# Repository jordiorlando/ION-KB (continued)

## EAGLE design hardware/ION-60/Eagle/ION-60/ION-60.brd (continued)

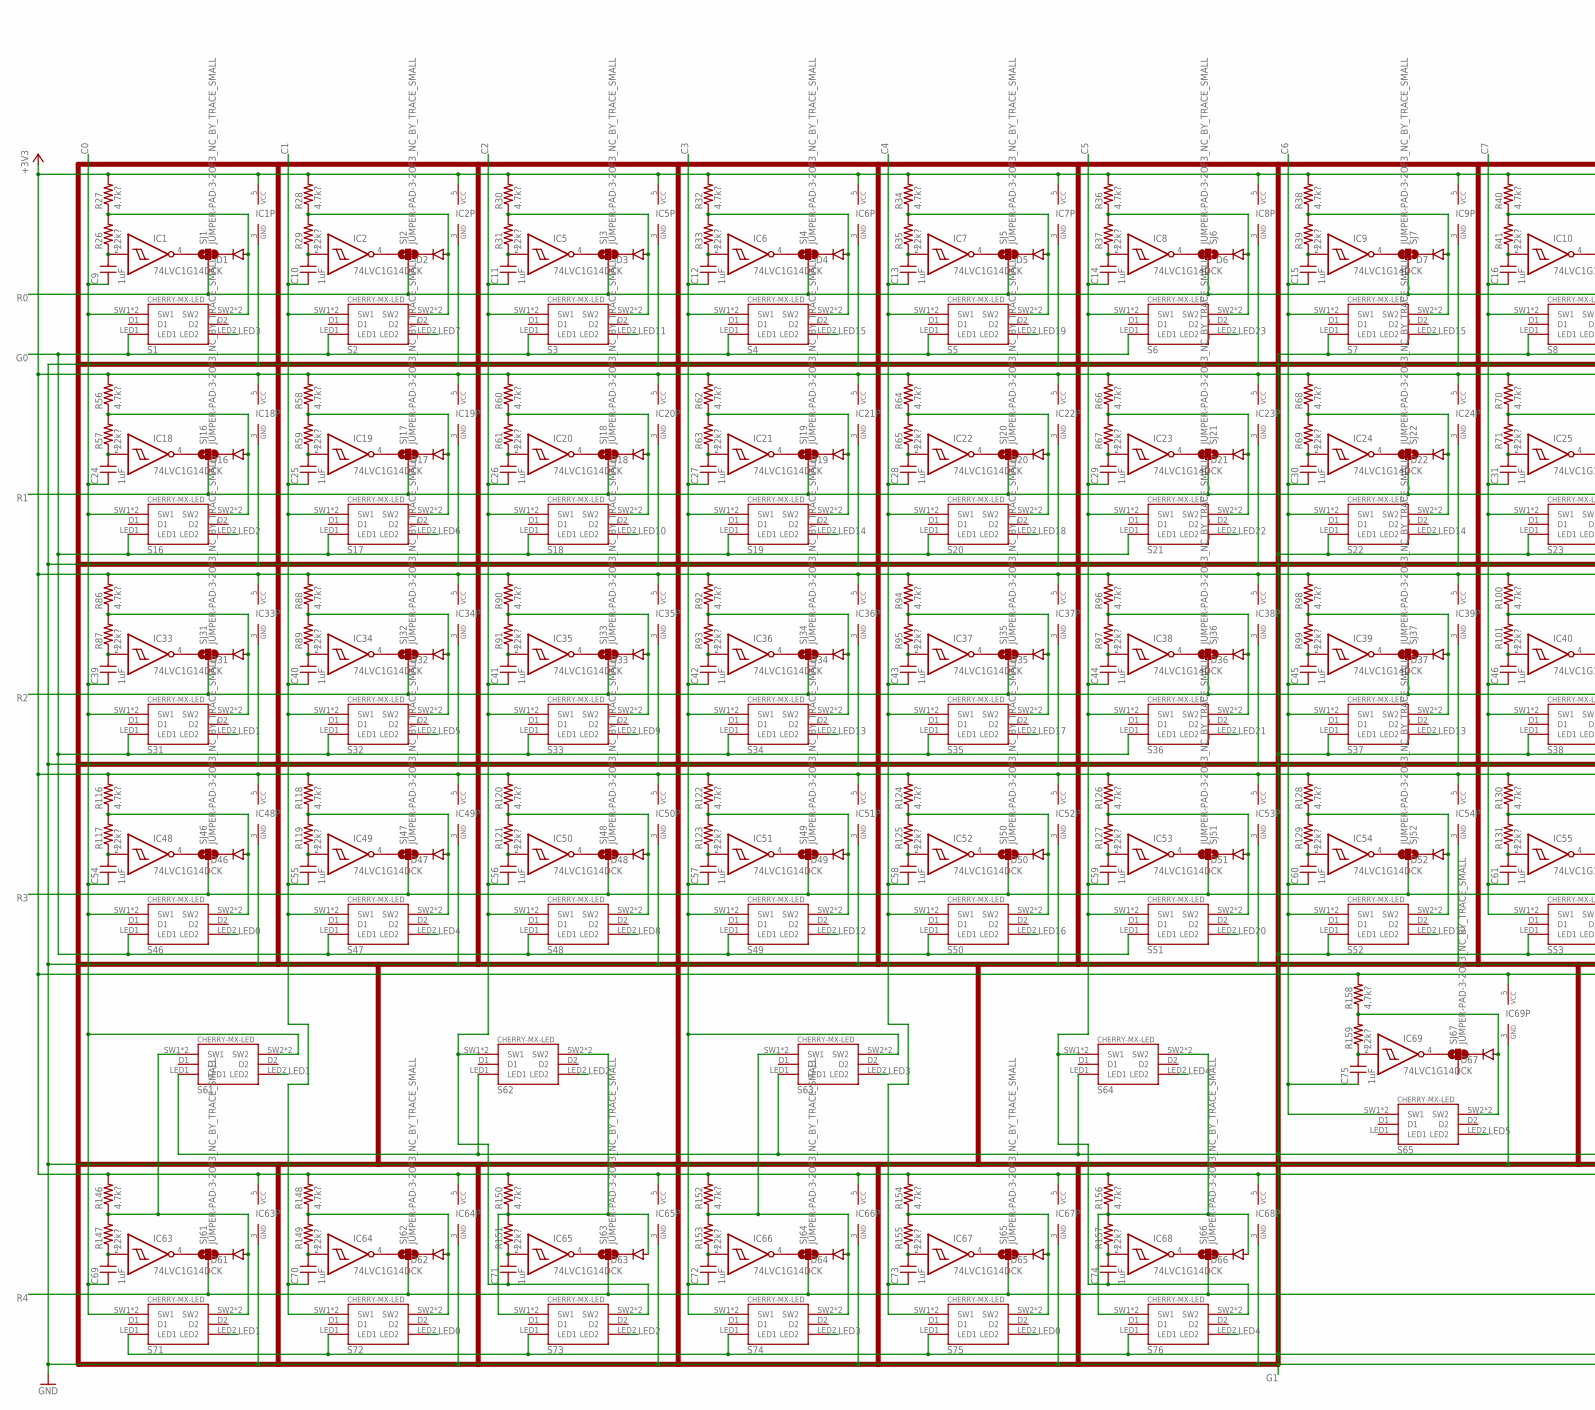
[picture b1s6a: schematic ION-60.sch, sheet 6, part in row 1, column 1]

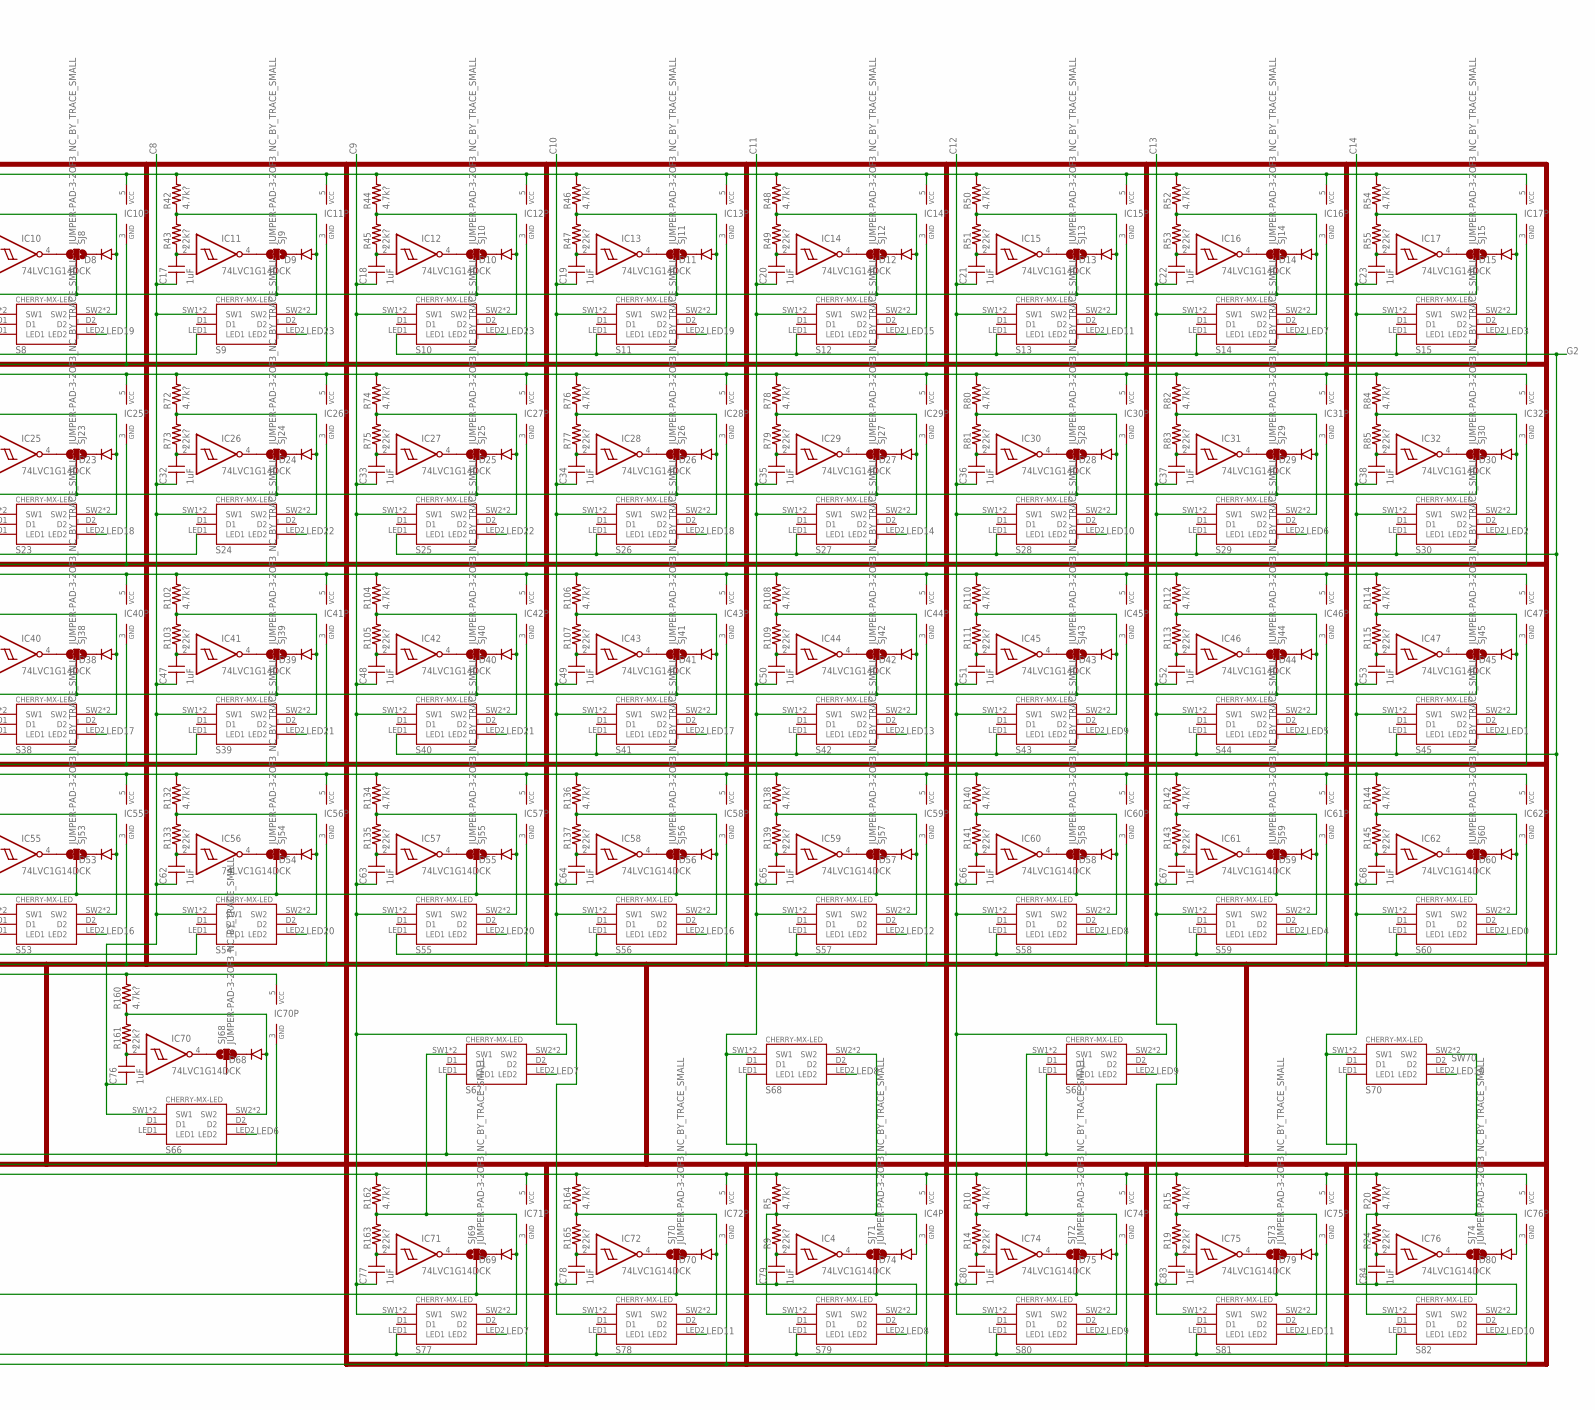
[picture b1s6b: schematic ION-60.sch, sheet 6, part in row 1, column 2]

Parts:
C9, C10, C11, C12, C13, C14, C15, C16, C17, C18, C19, C20, C21, C22, C23, C24, C25, C26, C27, C28, C29, C30, C31, C32, C33, C34, C35, C36, C37, C38, C39, C40, C41, C42, C43, C44, C45, C46, C47, C48, C49, C50, C51, C52, C53, C54, C55, C56, C57, C58, C59, C60, C61, C62, C63, C64, C65, C66, C67, C68, C69, C70, C71, C72, C73, C74, C75, C76, C77, C78, C79, C80, C83, C84: 1uF; C0603
D1, D2, D3, D4, D5, D6, D7, D8, D9, D10, D11, D12, D13, D14, D15, D16, D17, D18, D19, D20, D21, D22, D23, D24, D25, D26, D27, D28, D29, D30, D31, D32, D33, D34, D35, D36, D37, D38, D39, D40, D41, D42, D43, D44, D45, D46, D47, D48, D49, D50, D51, D52, D53, D54, D55, D56, D57, D58, D59, D60, D61, D62, D63, D64, D65, D66, D67, D68, D69, D70, D74, D75, D79, D80: DIODESOD123; SOD-123
IC1, IC2, IC4, IC5, IC6, IC7, IC8, IC9, IC10, IC11, IC12, IC13, IC14, IC15, IC16, IC17, IC18, IC19, IC20, IC21, IC22, IC23, IC24, IC25, IC26, IC27, IC28, IC29, IC30, IC31, IC32, IC33, IC34, IC35, IC36, IC37, IC38, IC39, IC40, IC41, IC42, IC43, IC44, IC45, IC46, IC47, IC48, IC49, IC50, IC51, IC52, IC53, IC54, IC55, IC56, IC57, IC58, IC59, IC60, IC61, IC62, IC63, IC64, IC65, IC66, IC67, IC68, IC69, IC70, IC71, IC72, IC74, IC75, IC76: 74LVC1G14DCK; SC70-5
R5, R10, R15, R20, R27, R28, R30, R32, R34, R36, R38, R40, R42, R44, R46, R48, R50, R52, R54, R56, R58, R60, R62, R64, R66, R68, R70, R72, R74, R76, R78, R80, R82, R84, R86, R88, R90, R92, R94, R96, R98, R100, R102, R104, R106, R108, R110, R112, R114, R116, R118, R120, R122, R124, R126, R128, R130, R132, R134, R136, R138, R140, R142, R144, R146, R148, R150, R152, R154, R156, R158, R160, R162, R164: 4.7k?; R0603
R9, R14, R19, R24, R26, R29, R31, R33, R35, R37, R39, R41, R43, R45, R47, R49, R51, R53, R55, R57, R59, R61, R63, R65, R67, R69, R71, R73, R75, R77, R79, R81, R83, R85, R87, R89, R91, R93, R95, R97, R99, R101, R103, R105, R107, R109, R111, R113, R115, R117, R119, R121, R123, R125, R127, R129, R131, R133, R135, R137, R139, R141, R143, R145, R147, R149, R151, R153, R155, R157, R159, R161, R163, R165: 22k?; R0603
S1, S2, S3, S4, S5, S6, S7, S8, S9, S10, S11, S12, S13, S14, S15, S16, S17, S18, S19, S20, S21, S22, S23, S24, S25, S26, S27, S28, S29, S30, S31, S32, S33, S34, S35, S36, S37, S38, S39, S40, S41, S42, S43, S44, S45, S46, S47, S48, S49, S50, S51, S52, S53, S54, S55, S56, S57, S58, S59, S60, S71, S72, S73, S74, S75, S76, S77, S78, S79, S80, S81, S82: CHERRY-MX-LED1X1; CHERRY-MX-LED-1X1
S61, S62, S63, S64, S65, S66, S67, S68, S69, S70: CHERRY-MX-LED1X1.5; CHERRY-MX-LED-1X1.5
SJ1, SJ2, SJ3, SJ4, SJ5, SJ6, SJ7, SJ8, SJ9, SJ10, SJ11, SJ12, SJ13, SJ14, SJ15, SJ16, SJ17, SJ18, SJ19, SJ20, SJ21, SJ22, SJ23, SJ24, SJ25, SJ26, SJ27, SJ28, SJ29, SJ30, SJ31, SJ32, SJ33, SJ34, SJ35, SJ36, SJ37, SJ38, SJ39, SJ40, SJ41, SJ42, SJ43, SJ44, SJ45, SJ46, SJ47, SJ48, SJ49, SJ50, SJ51, SJ52, SJ53, SJ54, SJ55, SJ56, SJ57, SJ58, SJ59, SJ60, SJ61, SJ62, SJ63, SJ64, SJ65, SJ66, SJ67, SJ68, SJ69, SJ70, SJ71, SJ72, SJ73, SJ74: JUMPER-PAD-3-2OF3_NC_BY_TRACE_SMALL; PAD-JUMPER-3-2OF3_NC_BY_TRACE_YES_SILK_FULL_BOX

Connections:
!COL: C9.2, IC1.2 (I), R26.1
!COL1: C10.2, IC2.2 (I), R29.1
!COL2: C11.2, IC5.2 (I), R31.1
!COL3: C12.2, IC6.2 (I), R33.1
!COL4: C13.2, IC7.2 (I), R35.1
!COL5: C14.2, IC8.2 (I), R37.1
!COL6: C15.2, IC9.2 (I), R39.1
!COL7: C16.2, IC10.2 (I), R41.1
!COL8: C17.2, IC11.2 (I), R43.1
!COL9: C18.2, IC12.2 (I), R45.1
!COL10: C19.2, IC13.2 (I), R47.1
!COL11: C20.2, IC14.2 (I), R49.1
!COL12: C21.2, IC15.2 (I), R51.1
!COL13: C22.2, IC16.2 (I), R53.1
!COL14: C23.2, IC17.2 (I), R55.1
!COL15: C24.2, IC18.2 (I), R57.1
!COL16: C25.2, IC19.2 (I), R59.1
!COL17: C26.2, IC20.2 (I), R61.1
!COL18: C27.2, IC21.2 (I), R63.1
!COL19: C28.2, IC22.2 (I), R65.1
!COL20: C29.2, IC23.2 (I), R67.1
!COL21: C30.2, IC24.2 (I), R69.1
!COL22: C31.2, IC25.2 (I), R71.1
!COL23: C32.2, IC26.2 (I), R73.1
!COL24: C33.2, IC27.2 (I), R75.1
!COL25: C34.2, IC28.2 (I), R77.1
!COL26: C35.2, IC29.2 (I), R79.1
!COL27: C36.2, IC30.2 (I), R81.1
!COL28: C37.2, IC31.2 (I), R83.1
!COL29: C38.2, IC32.2 (I), R85.1
!COL30: C39.2, IC33.2 (I), R87.1
!COL31: C40.2, IC34.2 (I), R89.1
!COL32: C41.2, IC35.2 (I), R91.1
!COL33: C42.2, IC36.2 (I), R93.1
!COL34: C43.2, IC37.2 (I), R95.1
!COL35: C44.2, IC38.2 (I), R97.1
!COL36: C45.2, IC39.2 (I), R99.1
!COL37: C46.2, IC40.2 (I), R101.1
!COL38: C47.2, IC41.2 (I), R103.1
!COL39: C48.2, IC42.2 (I), R105.1
!COL40: C49.2, IC43.2 (I), R107.1
!COL41: C50.2, IC44.2 (I), R109.1
!COL42: C51.2, IC45.2 (I), R111.1
!COL43: C52.2, IC46.2 (I), R113.1
!COL44: C53.2, IC47.2 (I), R115.1
!COL45: C54.2, IC48.2 (I), R117.1
!COL46: C55.2, IC49.2 (I), R119.1
!COL47: C56.2, IC50.2 (I), R121.1
!COL48: C57.2, IC51.2 (I), R123.1
!COL49: C58.2, IC52.2 (I), R125.1
!COL50: C59.2, IC53.2 (I), R127.1
!COL51: C60.2, IC54.2 (I), R129.1
!COL52: C61.2, IC55.2 (I), R131.1
!COL53: C62.2, IC56.2 (I), R133.1
!COL54: C63.2, IC57.2 (I), R135.1
!COL55: C64.2, IC58.2 (I), R137.1
!COL56: C65.2, IC59.2 (I), R139.1
!COL57: C66.2, IC60.2 (I), R141.1
!COL58: C67.2, IC61.2 (I), R143.1
!COL59: C68.2, IC62.2 (I), R145.1
!COL60: C69.2, IC63.2 (I), R147.1
!COL61: C70.2, IC64.2 (I), R149.1
!COL62: C71.2, IC65.2 (I), R151.1
!COL63: C72.2, IC66.2 (I), R153.1
!COL64: C73.2, IC67.2 (I), R155.1
!COL65: C74.2, IC68.2 (I), R157.1
!COL66: C75.2, IC69.2 (I), R159.1
!COL67: C76.2, IC70.2 (I), R161.1
!COL68: C77.2, IC71.2 (I), R163.1
!COL69: C78.2, IC72.2 (I), R165.1
!COL70: C79.2, IC4.2 (I), R9.1
!COL71: C80.2, IC74.2 (I), R14.1
!COL72: C83.2, IC75.2 (I), R19.1
!COL73: C84.2, IC76.2 (I), R24.1
+3V3: IC1.5 (VCC), IC2.5 (VCC), IC4.5 (VCC), IC5.5 (VCC), IC6.5 (VCC), IC7.5 (VCC), IC8.5 (VCC), IC9.5 (VCC), IC10.5 (VCC), IC11.5 (VCC), IC12.5 (VCC), IC13.5 (VCC), IC14.5 (VCC), IC15.5 (VCC), IC16.5 (VCC), IC17.5 (VCC), IC18.5 (VCC), IC19.5 (VCC), IC20.5 (VCC), IC21.5 (VCC), IC22.5 (VCC), IC23.5 (VCC), IC24.5 (VCC), IC25.5 (VCC), IC26.5 (VCC), IC27.5 (VCC), IC28.5 (VCC), IC29.5 (VCC), IC30.5 (VCC), IC31.5 (VCC), IC32.5 (VCC), IC33.5 (VCC), IC34.5 (VCC), IC35.5 (VCC), IC36.5 (VCC), IC37.5 (VCC), IC38.5 (VCC), IC39.5 (VCC), IC40.5 (VCC), IC41.5 (VCC), IC42.5 (VCC), IC43.5 (VCC), IC44.5 (VCC), IC45.5 (VCC), IC46.5 (VCC), IC47.5 (VCC), IC48.5 (VCC), IC49.5 (VCC), IC50.5 (VCC), IC51.5 (VCC), IC52.5 (VCC), IC53.5 (VCC), IC54.5 (VCC), IC55.5 (VCC), IC56.5 (VCC), IC57.5 (VCC), IC58.5 (VCC), IC59.5 (VCC), IC60.5 (VCC), IC61.5 (VCC), IC62.5 (VCC), IC63.5 (VCC), IC64.5 (VCC), IC65.5 (VCC), IC66.5 (VCC), IC67.5 (VCC), IC68.5 (VCC), IC69.5 (VCC), IC70.5 (VCC), IC71.5 (VCC), IC72.5 (VCC), IC74.5 (VCC), IC75.5 (VCC), IC76.5 (VCC), R5.2, R10.2, R15.2, R20.2, R27.2, R28.2, R30.2, R32.2, R34.2, R36.2, R38.2, R40.2, R42.2, R44.2, R46.2, R48.2, R50.2, R52.2, R54.2, R56.2, R58.2, R60.2, R62.2, R64.2, R66.2, R68.2, R70.2, R72.2, R74.2, R76.2, R78.2, R80.2, R82.2, R84.2, R86.2, R88.2, R90.2, R92.2, R94.2, R96.2, R98.2, R100.2, R102.2, R104.2, R106.2, R108.2, R110.2, R112.2, R114.2, R116.2, R118.2, R120.2, R122.2, R124.2, R126.2, R128.2, R130.2, R132.2, R134.2, R136.2, R138.2, R140.2, R142.2, R144.2, R146.2, R148.2, R150.2, R152.2, R154.2, R156.2, R158.2, R160.2, R162.2, R164.2; also elsewhere on the board
C0: C9.1, C24.1, C39.1, C54.1, C69.1, S1.SW1, S1.SW3 (SW1), S16.SW1, S16.SW3 (SW1), S31.SW1, S31.SW3 (SW1), S46.SW1, S46.SW3 (SW1), S61.SW2, S61.SW4 (SW2), S71.SW1, S71.SW3 (SW1); also elsewhere on the board
C1: C10.1, C25.1, C40.1, C55.1, C70.1, S2.SW1, S2.SW3 (SW1), S17.SW1, S17.SW3 (SW1), S32.SW1, S32.SW3 (SW1), S47.SW1, S47.SW3 (SW1), S72.SW1, S72.SW3 (SW1); also elsewhere on the board
C2: C11.1, C26.1, C41.1, C56.1, C71.1, S3.SW1, S3.SW3 (SW1), S18.SW1, S18.SW3 (SW1), S33.SW1, S33.SW3 (SW1), S48.SW1, S48.SW3 (SW1), S62.SW1, S62.SW3 (SW1), S73.SW2, S73.SW4 (SW2); also elsewhere on the board
C3: C12.1, C27.1, C42.1, C57.1, C72.1, S4.SW1, S4.SW3 (SW1), S19.SW1, S19.SW3 (SW1), S34.SW1, S34.SW3 (SW1), S49.SW1, S49.SW3 (SW1), S63.SW2, S63.SW4 (SW2), S74.SW1, S74.SW3 (SW1); also elsewhere on the board
C4: C13.1, C28.1, C43.1, C58.1, C73.1, S5.SW1, S5.SW3 (SW1), S20.SW1, S20.SW3 (SW1), S35.SW1, S35.SW3 (SW1), S50.SW1, S50.SW3 (SW1), S75.SW1, S75.SW3 (SW1); also elsewhere on the board
C5: C14.1, C29.1, C44.1, C59.1, C74.1, S6.SW1, S6.SW3 (SW1), S21.SW1, S21.SW3 (SW1), S36.SW1, S36.SW3 (SW1), S51.SW1, S51.SW3 (SW1), S64.SW1, S64.SW3 (SW1), S76.SW2, S76.SW4 (SW2); also elsewhere on the board
C6: C15.1, C30.1, C45.1, C60.1, C75.1, S7.SW1, S7.SW3 (SW1), S22.SW1, S22.SW3 (SW1), S37.SW1, S37.SW3 (SW1), S52.SW1, S52.SW3 (SW1), S65.SW1, S65.SW3 (SW1); also elsewhere on the board
C7: C16.1, C31.1, C46.1, C61.1, S8.SW1, S8.SW3 (SW1), S23.SW1, S23.SW3 (SW1), S38.SW1, S38.SW3 (SW1), S53.SW1, S53.SW3 (SW1); also elsewhere on the board
C8: C17.1, C32.1, C47.1, C62.1, C76.1, S9.SW1, S9.SW3 (SW1), S24.SW1, S24.SW3 (SW1), S39.SW1, S39.SW3 (SW1), S54.SW1, S54.SW3 (SW1), S66.SW1, S66.SW3 (SW1); also elsewhere on the board
C9: C18.1, C33.1, C48.1, C63.1, C77.1, S10.SW1, S10.SW3 (SW1), S25.SW1, S25.SW3 (SW1), S40.SW1, S40.SW3 (SW1), S55.SW1, S55.SW3 (SW1), S67.SW2, S67.SW4 (SW2), S77.SW1, S77.SW3 (SW1); also elsewhere on the board
C10: C19.1, C34.1, C49.1, C64.1, C78.1, S11.SW1, S11.SW3 (SW1), S26.SW1, S26.SW3 (SW1), S41.SW1, S41.SW3 (SW1), S56.SW1, S56.SW3 (SW1), S78.SW1, S78.SW3 (SW1); also elsewhere on the board
C11: C20.1, C35.1, C50.1, C65.1, C79.1, S12.SW1, S12.SW3 (SW1), S27.SW1, S27.SW3 (SW1), S42.SW1, S42.SW3 (SW1), S57.SW1, S57.SW3 (SW1), S68.SW1, S68.SW3 (SW1), S79.SW2, S79.SW4 (SW2); also elsewhere on the board
C12: C21.1, C36.1, C51.1, C66.1, C80.1, S13.SW1, S13.SW3 (SW1), S28.SW1, S28.SW3 (SW1), S43.SW1, S43.SW3 (SW1), S58.SW1, S58.SW3 (SW1), S69.SW2, S69.SW4 (SW2), S80.SW1, S80.SW3 (SW1); also elsewhere on the board
C13: C22.1, C37.1, C52.1, C67.1, C83.1, S14.SW1, S14.SW3 (SW1), S29.SW1, S29.SW3 (SW1), S44.SW1, S44.SW3 (SW1), S59.SW1, S59.SW3 (SW1), S81.SW1, S81.SW3 (SW1); also elsewhere on the board
C14: C23.1, C38.1, C53.1, C68.1, C84.1, S15.SW1, S15.SW3 (SW1), S30.SW1, S30.SW3 (SW1), S45.SW1, S45.SW3 (SW1), S60.SW1, S60.SW3 (SW1), S70.SW1, S70.SW3 (SW1), S82.SW2, S82.SW4 (SW2); also elsewhere on the board
G0: S1.LED1, S2.LED1, S3.LED1, S4.LED1, S5.LED1, S6.LED1, S16.LED1, S17.LED1, S18.LED1, S19.LED1, S20.LED1, S21.LED1, S31.LED1, S32.LED1, S33.LED1, S34.LED1, S35.LED1, S36.LED1, S46.LED1, S47.LED1, S48.LED1, S49.LED1, S50.LED1, S51.LED1; also elsewhere on the board
G1: S7.LED1, S8.LED1, S9.LED1, S22.LED1, S23.LED1, S24.LED1, S37.LED1, S38.LED1, S39.LED1, S52.LED1, S53.LED1, S54.LED1, S61.LED1, S62.LED1, S63.LED1, S64.LED1, S67.LED1, S68.LED1, S69.LED1, S70.LED1, S71.LED1, S72.LED1, S73.LED1, S74.LED1, S75.LED1, S76.LED1, S77.LED1, S78.LED1, S79.LED1, S80.LED1, S81.LED1, S82.LED1; also elsewhere on the board
G2: S10.LED1, S11.LED1, S12.LED1, S13.LED1, S14.LED1, S15.LED1, S25.LED1, S26.LED1, S27.LED1, S28.LED1, S29.LED1, S30.LED1, S40.LED1, S41.LED1, S42.LED1, S43.LED1, S44.LED1, S45.LED1, S55.LED1, S56.LED1, S57.LED1, S58.LED1, S59.LED1, S60.LED1; also elsewhere on the board
GND: IC1.3 (GND), IC2.3 (GND), IC4.3 (GND), IC5.3 (GND), IC6.3 (GND), IC7.3 (GND), IC8.3 (GND), IC9.3 (GND), IC10.3 (GND), IC11.3 (GND), IC12.3 (GND), IC13.3 (GND), IC14.3 (GND), IC15.3 (GND), IC16.3 (GND), IC17.3 (GND), IC18.3 (GND), IC19.3 (GND), IC20.3 (GND), IC21.3 (GND), IC22.3 (GND), IC23.3 (GND), IC24.3 (GND), IC25.3 (GND), IC26.3 (GND), IC27.3 (GND), IC28.3 (GND), IC29.3 (GND), IC30.3 (GND), IC31.3 (GND), IC32.3 (GND), IC33.3 (GND), IC34.3 (GND), IC35.3 (GND), IC36.3 (GND), IC37.3 (GND), IC38.3 (GND), IC39.3 (GND), IC40.3 (GND), IC41.3 (GND), IC42.3 (GND), IC43.3 (GND), IC44.3 (GND), IC45.3 (GND), IC46.3 (GND), IC47.3 (GND), IC48.3 (GND), IC49.3 (GND), IC50.3 (GND), IC51.3 (GND), IC52.3 (GND), IC53.3 (GND), IC54.3 (GND), IC55.3 (GND), IC56.3 (GND), IC57.3 (GND), IC58.3 (GND), IC59.3 (GND), IC60.3 (GND), IC61.3 (GND), IC62.3 (GND), IC63.3 (GND), IC64.3 (GND), IC65.3 (GND), IC66.3 (GND), IC67.3 (GND), IC68.3 (GND), IC69.3 (GND), IC70.3 (GND), IC71.3 (GND), IC72.3 (GND), IC74.3 (GND), IC75.3 (GND), IC76.3 (GND); also elsewhere on the board
LED0: S46.LED2, S60.LED2, S72.LED2, S75.LED2; also elsewhere on the board
LED1: S31.LED2, S45.LED2, S61.LED2, S71.LED2; also elsewhere on the board
LED2: S16.LED2, S30.LED2, S62.LED2, S73.LED2; also elsewhere on the board
LED3: S1.LED2, S15.LED2, S63.LED2, S74.LED2; also elsewhere on the board
LED4: S47.LED2, S59.LED2, S64.LED2, S76.LED2; also elsewhere on the board
LED5: S32.LED2, S44.LED2, S65.LED2; also elsewhere on the board
LED6: S17.LED2, S29.LED2, S66.LED2; also elsewhere on the board
LED7: S2.LED2, S14.LED2, S67.LED2, S77.LED2; also elsewhere on the board
LED8: S48.LED2, S58.LED2, S68.LED2, S79.LED2; also elsewhere on the board
LED9: S33.LED2, S43.LED2, S69.LED2, S80.LED2; also elsewhere on the board
LED10: S18.LED2, S28.LED2, S70.LED2, S82.LED2; also elsewhere on the board
LED11: S3.LED2, S13.LED2, S78.LED2, S81.LED2; also elsewhere on the board
LED12: S49.LED2, S52.LED2, S57.LED2; also elsewhere on the board
LED13: S34.LED2, S37.LED2, S42.LED2; also elsewhere on the board
LED14: S19.LED2, S22.LED2, S27.LED2; also elsewhere on the board
LED15: S4.LED2, S7.LED2, S12.LED2; also elsewhere on the board
LED16: S50.LED2, S53.LED2, S56.LED2; also elsewhere on the board
LED17: S35.LED2, S38.LED2, S41.LED2; also elsewhere on the board
LED18: S20.LED2, S23.LED2, S26.LED2; also elsewhere on the board
LED19: S5.LED2, S8.LED2, S11.LED2; also elsewhere on the board
LED20: S51.LED2, S54.LED2, S55.LED2; also elsewhere on the board
LED21: S36.LED2, S39.LED2, S40.LED2; also elsewhere on the board
LED22: S21.LED2, S24.LED2, S25.LED2; also elsewhere on the board
LED23: S6.LED2, S9.LED2, S10.LED2; also elsewhere on the board
unnamed: D31.A, R86.1, R87.2, S31.SW2, S31.SW4 (SW2)
unnamed: D32.A, R88.1, R89.2, S32.SW2, S32.SW4 (SW2)
unnamed: D33.A, R90.1, R91.2, S33.SW2, S33.SW4 (SW2)
unnamed: D34.A, R92.1, R93.2, S34.SW2, S34.SW4 (SW2)
unnamed: D1.C, SJ1.3
unnamed: IC8.4 (O), SJ6.3
unnamed: IC9.4 (O), SJ7.3
unnamed: IC10.4 (O), SJ8.3
unnamed: D66.C, SJ66.3
unnamed: D2.C, SJ2.3
unnamed: IC11.4 (O), SJ9.3
unnamed: IC12.4 (O), SJ10.3
unnamed: IC13.4 (O), SJ11.3
unnamed: IC14.4 (O), SJ12.3
unnamed: IC15.4 (O), SJ13.3
unnamed: IC16.4 (O), SJ14.3
unnamed: IC17.4 (O), SJ15.3
unnamed: D35.A, R94.1, R95.2, S35.SW2, S35.SW4 (SW2)
unnamed: D36.A, R96.1, R97.2, S36.SW2, S36.SW4 (SW2)
unnamed: D37.A, R98.1, R99.2, S37.SW2, S37.SW4 (SW2)
unnamed: D38.A, R100.1, R101.2, S38.SW2, S38.SW4 (SW2)
unnamed: D39.A, R102.1, R103.2, S39.SW2, S39.SW4 (SW2)
unnamed: IC1.4 (O), SJ1.1
unnamed: IC2.4 (O), SJ2.1
unnamed: D40.A, R104.1, R105.2, S40.SW2, S40.SW4 (SW2)
unnamed: D41.A, R106.1, R107.2, S41.SW2, S41.SW4 (SW2)
unnamed: D42.A, R108.1, R109.2, S42.SW2, S42.SW4 (SW2)
unnamed: D3.C, SJ3.3
unnamed: IC5.4 (O), SJ3.1
unnamed: D4.C, SJ4.3
unnamed: D43.A, R110.1, R111.2, S43.SW2, S43.SW4 (SW2)
unnamed: D6.C, SJ6.1
unnamed: D7.C, SJ7.1
unnamed: IC6.4 (O), SJ4.1
unnamed: D44.A, R112.1, R113.2, S44.SW2, S44.SW4 (SW2)
unnamed: D5.C, SJ5.3
unnamed: IC7.4 (O), SJ5.1
unnamed: D8.C, SJ8.1
unnamed: D9.C, SJ9.1
unnamed: D10.C, SJ10.1
unnamed: D45.A, R114.1, R115.2, S45.SW2, S45.SW4 (SW2)
unnamed: D11.C, SJ11.1
unnamed: D16.C, SJ16.3
unnamed: D12.C, SJ12.1
unnamed: D13.C, SJ13.1
unnamed: D14.C, SJ14.1
unnamed: D15.C, SJ15.1
unnamed: IC18.4 (O), SJ16.1
unnamed: D17.C, SJ17.3
unnamed: IC19.4 (O), SJ17.1
unnamed: D18.C, SJ18.3
unnamed: IC20.4 (O), SJ18.1
unnamed: IC23.4 (O), SJ21.3
unnamed: IC24.4 (O), SJ22.3
unnamed: IC25.4 (O), SJ23.3
unnamed: D19.C, SJ19.3
unnamed: IC26.4 (O), SJ24.3
unnamed: IC27.4 (O), SJ25.3
unnamed: IC28.4 (O), SJ26.3
unnamed: IC29.4 (O), SJ27.3
unnamed: IC30.4 (O), SJ28.3
unnamed: IC31.4 (O), SJ29.3
unnamed: IC32.4 (O), SJ30.3
unnamed: D30.C, SJ30.1
unnamed: D29.C, SJ29.1
unnamed: D28.C, SJ28.1
unnamed: D27.C, SJ27.1
unnamed: D26.C, SJ26.1
unnamed: D25.C, SJ25.1
unnamed: D24.C, SJ24.1
unnamed: D23.C, SJ23.1
unnamed: D22.C, SJ22.1
unnamed: D21.C, SJ21.1
unnamed: IC21.4 (O), SJ19.1
unnamed: D20.C, SJ20.3
unnamed: IC22.4 (O), SJ20.1
unnamed: D32.C, SJ32.3
unnamed: D31.C, SJ31.3
unnamed: D61.A, R146.1, R147.2, S61.SW1, S61.SW3 (SW1), S71.SW2, S71.SW4 (SW2)
unnamed: IC68.4 (O), SJ66.1
unnamed: D65.C, SJ65.3
unnamed: IC67.4 (O), SJ65.1
unnamed: D64.C, SJ64.3
unnamed: IC66.4 (O), SJ64.1
unnamed: D63.C, SJ63.3
unnamed: IC65.4 (O), SJ63.1
unnamed: D62.C, SJ62.3
unnamed: IC64.4 (O), SJ62.1
unnamed: D61.C, SJ61.3
unnamed: IC63.4 (O), SJ61.1
unnamed: IC33.4 (O), SJ31.1
unnamed: IC34.4 (O), SJ32.1
unnamed: D33.C, SJ33.3
unnamed: IC35.4 (O), SJ33.1
unnamed: D34.C, SJ34.3
unnamed: IC53.4 (O), SJ51.3
unnamed: IC54.4 (O), SJ52.3
unnamed: IC55.4 (O), SJ53.3
unnamed: IC56.4 (O), SJ54.3
unnamed: IC57.4 (O), SJ55.3
unnamed: IC58.4 (O), SJ56.3
unnamed: IC36.4 (O), SJ34.1
unnamed: D35.C, SJ35.3
unnamed: IC37.4 (O), SJ35.1
unnamed: IC38.4 (O), SJ36.3
unnamed: IC39.4 (O), SJ37.3
unnamed: IC40.4 (O), SJ38.3
unnamed: IC41.4 (O), SJ39.3
unnamed: IC42.4 (O), SJ40.3
unnamed: IC43.4 (O), SJ41.3
unnamed: IC44.4 (O), SJ42.3
unnamed: IC45.4 (O), SJ43.3
unnamed: IC46.4 (O), SJ44.3
unnamed: IC47.4 (O), SJ45.3
unnamed: D46.C, SJ46.3
unnamed: D47.C, SJ47.3
unnamed: IC59.4 (O), SJ57.3
unnamed: IC60.4 (O), SJ58.3
unnamed: IC61.4 (O), SJ59.3
unnamed: IC62.4 (O), SJ60.3
unnamed: D69.C, SJ69.3
unnamed: IC71.4 (O), SJ69.1
unnamed: D70.C, SJ70.3
unnamed: IC72.4 (O), SJ70.1
unnamed: D67.C, SJ67.3
unnamed: IC69.4 (O), SJ67.1
unnamed: D68.C, SJ68.3
unnamed: IC70.4 (O), SJ68.1
unnamed: D74.C, SJ71.3
unnamed: IC4.4 (O), SJ71.1
unnamed: D75.C, SJ72.3
unnamed: IC74.4 (O), SJ72.1
unnamed: D79.C, SJ73.3
unnamed: IC75.4 (O), SJ73.1
unnamed: D80.C, SJ74.3
unnamed: IC76.4 (O), SJ74.1
unnamed: D80.A, R20.1, R24.2, S70.SW2, S70.SW4 (SW2), S82.SW1, S82.SW3 (SW1)
unnamed: D60.C, SJ60.1
unnamed: D59.C, SJ59.1
unnamed: D58.C, SJ58.1
unnamed: D57.C, SJ57.1
unnamed: D56.C, SJ56.1
unnamed: D55.C, SJ55.1
unnamed: D54.C, SJ54.1
unnamed: D53.C, SJ53.1
unnamed: D52.C, SJ52.1
unnamed: D51.C, SJ51.1
unnamed: IC49.4 (O), SJ47.1
unnamed: D48.C, SJ48.3
unnamed: IC50.4 (O), SJ48.1
unnamed: D49.C, SJ49.3
unnamed: IC48.4 (O), SJ46.1
unnamed: IC51.4 (O), SJ49.1
unnamed: D50.C, SJ50.3
unnamed: IC52.4 (O), SJ50.1
unnamed: D36.C, SJ36.1
unnamed: D37.C, SJ37.1
unnamed: D38.C, SJ38.1
unnamed: D39.C, SJ39.1
unnamed: D40.C, SJ40.1
unnamed: D41.C, SJ41.1
unnamed: D42.C, SJ42.1
unnamed: D43.C, SJ43.1
unnamed: D44.C, SJ44.1
unnamed: D45.C, SJ45.1
R0: SJ1.2, SJ2.2, SJ3.2, SJ4.2, SJ5.2, SJ6.2, SJ7.2, SJ8.2, SJ9.2, SJ10.2, SJ11.2, SJ12.2, SJ13.2, SJ14.2, SJ15.2; also elsewhere on the board
R1: SJ16.2, SJ17.2, SJ18.2, SJ19.2, SJ20.2, SJ21.2, SJ22.2, SJ23.2, SJ24.2, SJ25.2, SJ26.2, SJ27.2, SJ28.2, SJ29.2, SJ30.2; also elsewhere on the board
R2: SJ31.2, SJ32.2, SJ33.2, SJ34.2, SJ35.2, SJ36.2, SJ37.2, SJ38.2, SJ39.2, SJ40.2, SJ41.2, SJ42.2, SJ43.2, SJ44.2, SJ45.2; also elsewhere on the board
R3: SJ46.2, SJ47.2, SJ48.2, SJ49.2, SJ50.2, SJ51.2, SJ52.2, SJ53.2, SJ54.2, SJ55.2, SJ56.2, SJ57.2, SJ58.2, SJ59.2, SJ60.2; also elsewhere on the board
R4: SJ61.2, SJ62.2, SJ63.2, SJ64.2, SJ65.2, SJ66.2, SJ69.2, SJ70.2, SJ71.2, SJ72.2, SJ73.2, SJ74.2; also elsewhere on the board
SW1: D1.A, R26.2, R27.1, S1.SW2, S1.SW4 (SW2)
SW2: D2.A, R28.1, R29.2, S2.SW2, S2.SW4 (SW2)
SW3: D3.A, R30.1, R31.2, S3.SW2, S3.SW4 (SW2)
SW4: D4.A, R32.1, R33.2, S4.SW2, S4.SW4 (SW2)
SW5: D5.A, R34.1, R35.2, S5.SW2, S5.SW4 (SW2)
SW6: D6.A, R36.1, R37.2, S6.SW2, S6.SW4 (SW2)
SW7: D7.A, R38.1, R39.2, S7.SW2, S7.SW4 (SW2)
SW8: D8.A, R40.1, R41.2, S8.SW2, S8.SW4 (SW2)
SW9: D9.A, R42.1, R43.2, S9.SW2, S9.SW4 (SW2)
SW10: D10.A, R44.1, R45.2, S10.SW2, S10.SW4 (SW2)
SW11: D11.A, R46.1, R47.2, S11.SW2, S11.SW4 (SW2)
SW12: D12.A, R48.1, R49.2, S12.SW2, S12.SW4 (SW2)
SW13: D13.A, R50.1, R51.2, S13.SW2, S13.SW4 (SW2)
SW14: D14.A, R52.1, R53.2, S14.SW2, S14.SW4 (SW2)
SW15: D15.A, R54.1, R55.2, S15.SW2, S15.SW4 (SW2)
SW16: D16.A, R56.1, R57.2, S16.SW2, S16.SW4 (SW2)
SW17: D17.A, R58.1, R59.2, S17.SW2, S17.SW4 (SW2)
SW18: D18.A, R60.1, R61.2, S18.SW2, S18.SW4 (SW2)
SW19: D19.A, R62.1, R63.2, S19.SW2, S19.SW4 (SW2)
SW20: D20.A, R64.1, R65.2, S20.SW2, S20.SW4 (SW2)
SW21: D21.A, R66.1, R67.2, S21.SW2, S21.SW4 (SW2)
SW22: D22.A, R68.1, R69.2, S22.SW2, S22.SW4 (SW2)
SW23: D23.A, R70.1, R71.2, S23.SW2, S23.SW4 (SW2)
SW24: D24.A, R72.1, R73.2, S24.SW2, S24.SW4 (SW2)
SW25: D25.A, R74.1, R75.2, S25.SW2, S25.SW4 (SW2)
SW26: D26.A, R76.1, R77.2, S26.SW2, S26.SW4 (SW2)
SW27: D27.A, R78.1, R79.2, S27.SW2, S27.SW4 (SW2)
SW28: D28.A, R80.1, R81.2, S28.SW2, S28.SW4 (SW2)
SW29: D29.A, R82.1, R83.2, S29.SW2, S29.SW4 (SW2)
SW30: D30.A, R84.1, R85.2, S30.SW2, S30.SW4 (SW2)
SW46: D46.A, R116.1, R117.2, S46.SW2, S46.SW4 (SW2)
SW47: D47.A, R118.1, R119.2, S47.SW2, S47.SW4 (SW2)
SW48: D48.A, R120.1, R121.2, S48.SW2, S48.SW4 (SW2)
SW49: D49.A, R122.1, R123.2, S49.SW2, S49.SW4 (SW2)
SW50: D50.A, R124.1, R125.2, S50.SW2, S50.SW4 (SW2)
SW51: D51.A, R126.1, R127.2, S51.SW2, S51.SW4 (SW2)
SW52: D52.A, R128.1, R129.2, S52.SW2, S52.SW4 (SW2)
SW53: D53.A, R130.1, R131.2, S53.SW2, S53.SW4 (SW2)
SW54: D54.A, R132.1, R133.2, S54.SW2, S54.SW4 (SW2)
SW55: D55.A, R134.1, R135.2, S55.SW2, S55.SW4 (SW2)
SW56: D56.A, R136.1, R137.2, S56.SW2, S56.SW4 (SW2)
SW57: D57.A, R138.1, R139.2, S57.SW2, S57.SW4 (SW2)
SW58: D58.A, R140.1, R141.2, S58.SW2, S58.SW4 (SW2)
SW59: D59.A, R142.1, R143.2, S59.SW2, S59.SW4 (SW2)
SW60: D60.A, R144.1, R145.2, S60.SW2, S60.SW4 (SW2)
SW61: D74.A, R5.1, R9.2, S68.SW2, S68.SW4 (SW2), S79.SW1, S79.SW3 (SW1)
SW62: D62.A, R148.1, R149.2, S72.SW2, S72.SW4 (SW2)
SW63: D63.A, R150.1, R151.2, S62.SW2, S62.SW4 (SW2), S73.SW1, S73.SW3 (SW1)
SW64: D64.A, R152.1, R153.2, S63.SW1, S63.SW3 (SW1), S74.SW2, S74.SW4 (SW2)
SW65: D65.A, R154.1, R155.2, S75.SW2, S75.SW4 (SW2)
SW66: D66.A, R156.1, R157.2, S64.SW2, S64.SW4 (SW2), S76.SW1, S76.SW3 (SW1)
SW67: D67.A, R158.1, R159.2, S65.SW2, S65.SW4 (SW2)
SW68: D68.A, R160.1, R161.2, S66.SW2, S66.SW4 (SW2)
SW69: D69.A, R162.1, R163.2, S67.SW1, S67.SW3 (SW1), S77.SW2, S77.SW4 (SW2)
SW70: D70.A, R164.1, R165.2, S78.SW2, S78.SW4 (SW2)
SW71: D75.A, R10.1, R14.2, S69.SW1, S69.SW3 (SW1), S80.SW2, S80.SW4 (SW2)
SW72: D79.A, R15.1, R19.2, S81.SW2, S81.SW4 (SW2)

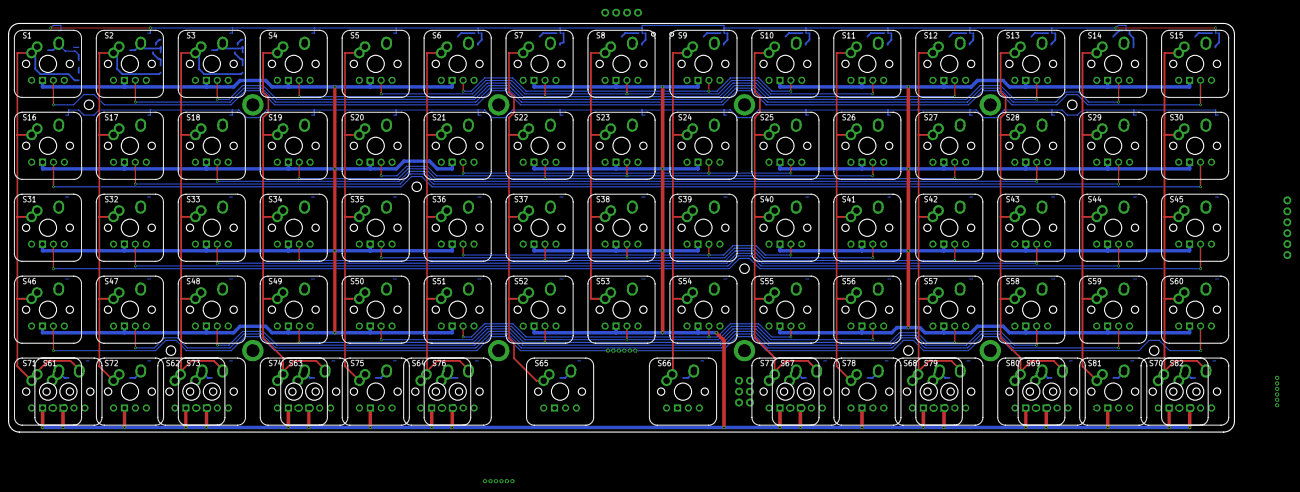
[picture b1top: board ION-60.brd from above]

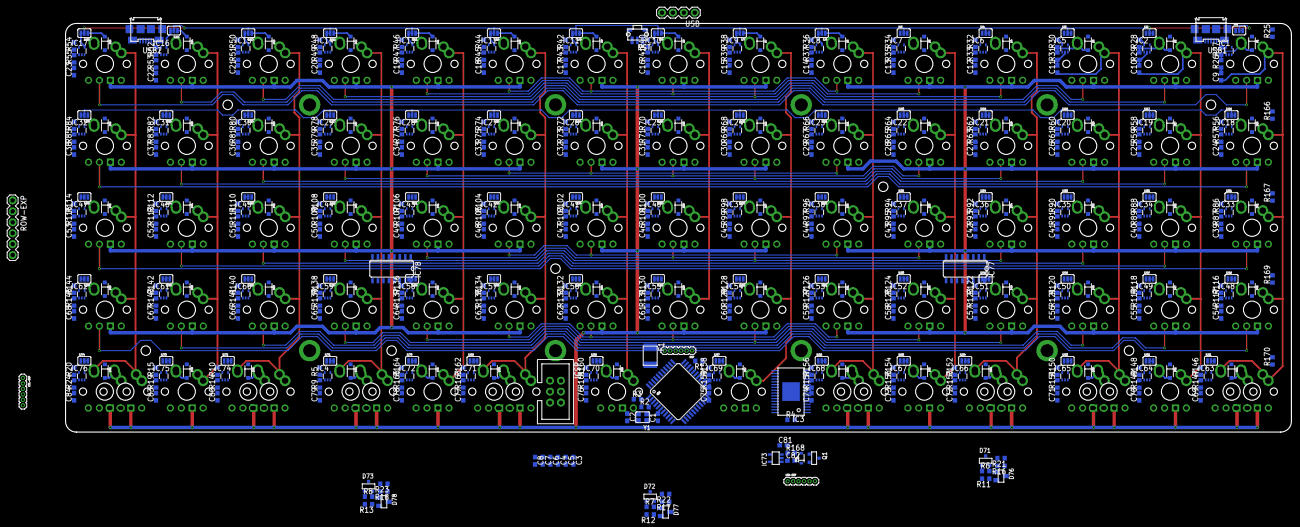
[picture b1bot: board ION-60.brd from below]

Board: 2 copper layers, 285.0 x 95.0 mm, 582 parts (500 on the bottom side), 390 nets.

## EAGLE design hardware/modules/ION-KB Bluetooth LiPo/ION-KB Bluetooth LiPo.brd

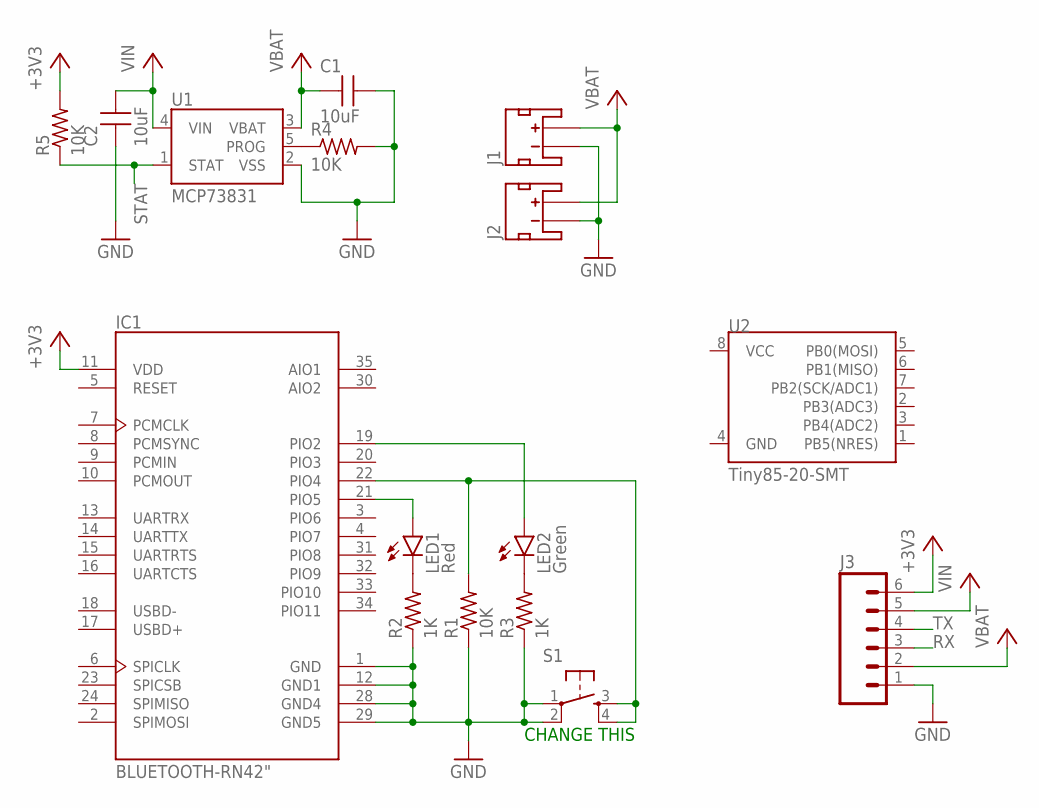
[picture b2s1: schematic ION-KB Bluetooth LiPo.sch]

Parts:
C1, C2: 10uF; C0603
IC1: BLUETOOTH-RN42"; RN42
J1, J2: JST_2MM_MALE; JST-2-SMD
J3: 1X06M-0.05-PTH; M-1X06-0.05-PTH
LED1: Red; L0603
LED2: Green; L0603
R1, R4, R5: 10K; R0603
R2, R3: 1K; R0603
S1: SWITCH-TACTILESMD; SWITCH-TACTILE-SMD
U1: MCP73831; SOT23-5
U2: Tiny85-20-SMT; SO08-EIAJ

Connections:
+3V3: IC1.11 (VDD), J3.6, R5.2
GND: C1.2, C2.1, IC1.1 (GND), IC1.12 (GND1), IC1.28 (GND4), IC1.29 (GND5), J1.1 (-), J2.1 (-), J3.1, R1.1, R2.1, R3.1, R4.2, S1.1, S1.2, U1.2 (VSS)
unnamed: IC1.22 (PIO4), R1.2, S1.3, S1.4
unnamed: LED1.C, R2.2
unnamed: IC1.21 (PIO5), LED1.A
unnamed: IC1.19 (PIO2), LED2.A
unnamed: LED2.C, R3.2
unnamed: R4.1, U1.5 (PROG)
RX: J3.3
STAT: R5.1, U1.1 (STAT)
TX: J3.4
VBAT: C1.1, J1.2 (+), J2.2 (+), J3.2, U1.3 (VBAT)
VIN: C2.2, J3.5, U1.4 (VIN)

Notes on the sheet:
CHANGE THIS

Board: 2 copper layers, 16 parts (0 on the bottom side), 11 nets, no tracks yet.

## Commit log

2015-04-10 More work on new design
2015-04-16 Add ergo layout
2015-04-16 More work on ortholinear PCB
2015-04-17 Update gitignore
2015-04-17 More changes
2015-05-06 Changes for new layout
2015-05-08 Finish up basic v0.2 design
2015-05-09 More changes, fix versioning
2015-05-14 Add wrist wrest
2015-05-15 Lots more work
2015-05-20 Lots o' changes
2015-05-21 More changes, fix some dimensions
2015-05-21 Edit PCB
2015-05-29 Compile datasheets
2015-05-29 More changes...I think
2015-05-29 Further additions to PCB
2015-06-05 First FreeCAD model
2015-06-08 More work on PCB
2015-06-08 More changes to FreeCAD
2015-06-08 Big change for manufacturability (split case design)
2015-06-09 Initial Antimony model
2015-06-09 Add bluetooth module
2015-06-09 Add USB module
2015-06-10 Update bluetooth module
2015-06-10 Update RGB board
2015-06-10 Lots more work on main PCB
2015-06-10 Add more datasheets
2015-06-10 Add link to Google Doc
2015-06-20 Add editor layouts
2015-06-20 Switch to single RGB LED
2015-06-20 Add LED pin datasheet
2015-07-22 Hardware debouncing and 5V VCC
2015-07-22 Back to 3V3 because LiPo
2015-07-22 Ignore gerber files
2015-07-22 Add panelized RGB LED
2015-07-22 Remove VREG from Bluetooth board
2015-07-22 Add silkscreen
2015-07-27 Add silkscreen labels
2015-07-27 More work, maybe removing RGB LEDs after this
2015-07-27 Unknown changes
2015-07-28 Remove RGB LEDs, change reset switch
2015-08-12 More work
